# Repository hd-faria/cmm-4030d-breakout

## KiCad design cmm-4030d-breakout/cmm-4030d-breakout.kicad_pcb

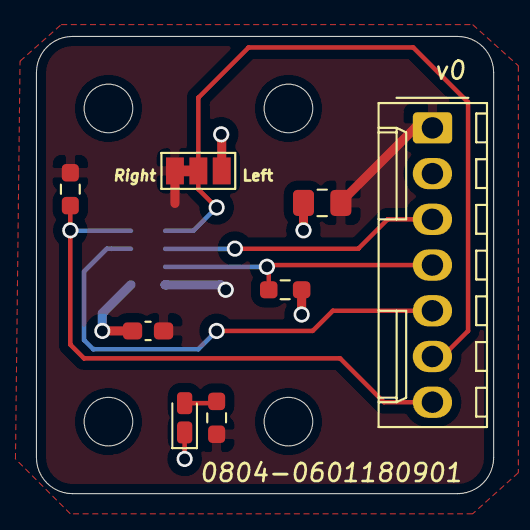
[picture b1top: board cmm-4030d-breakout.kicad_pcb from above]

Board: 2 copper layers, 25.4 x 25.4 mm, 13 parts (1 on the bottom side), 8 nets.

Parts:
C1: 0.1uF; C_0603_1608Metric_Pad1.08x0.95mm_HandSolder
C2: 10uF; C_0805_2012Metric_Pad1.18x1.45mm_HandSolder
D1: LED_Small; LED_0603_1608Metric_Castellated
H1, H2, H3, H4: MountingHole; MountingHole_2.7mm_M2.5
J1: Conn_01x07_Female; Molex_KK-254_AE-6410-07A_1x07_P2.54mm_Vertical
JP1: Jumper_3_Bridged12; SolderJumper-3_P1.3mm_Bridged12_Pad1.0x1.5mm_NumberLabels
MK1: CMM-4030D-261-I2S-TR; MIC_CMM-4030D-261-I2S-TR
R1: 100k; R_0603_1608Metric_Pad0.98x0.95mm_HandSolder
R2, R3: 1k; R_0603_1608Metric_Pad0.98x0.95mm_HandSolder

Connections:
/CE: J1.7, MK1.4, R2.2
/DOUT: J1.4, MK1.7, R1.1
/SCK: J1.3, MK1.6
/SELECT: J1.6, JP1.2, MK1.5
/WS: J1.5, MK1.3
GNDREF: C1.2, C2.2, D1.1, J1.2, JP1.3, MK1.1, R1.2
unnamed: D1.2, R3.2
VDD: C1.1, C2.1, J1.1, JP1.1, MK1.8, R2.1, R3.1

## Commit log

2021-10-28 add current content
2021-10-29 pcb update
